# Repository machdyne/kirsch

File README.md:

# Kirsch Computer

Kirsch is an FPGA computer designed by Lone Dynamics Corporation.

This repo will contain schematics, PCB layouts, pinouts, a 3D-printable case, example gateware and documentation.

Find more information on the [Kirsch product page](https://machdyne.com/product/kirsch-computer/).

## Programming Kirsch

Kirsch has a JTAG interface that can be used to program the SRAM or the included flash [MMOD](https://machdyne.com/product/mmod).

### JTAG

These examples assume you're using a "USB Blaster" JTAG cable, see the header pinout below. You will need to have [openFPGALoader](https://github.com/trabucayre/openFPGALoader) installed.

Program the configuration SRAM:

```
openFPGALoader -c usb-blaster blinky.bit
```

Program the flash MMOD:

```
openFPGALoader -f -c usb-blaster blinky.bit --fpga-part xc7a35tftg256
```

## Blinky 

Building the blinky example requires Vivado or [openxc7](https://github.com/openxc7).

Assuming they are installed, you can simply type `make blinky_openxc7` or `make blinky_vivado` to build the gateware, which will be written to output/blinky.bit. You can then use [openFPGALoader](https://github.com/trabucayre/openFPGALoader) to write the gateware to the device.

## Linux

See the [Kakao Linux](https://github.com/machdyne/kakao) repo for the latest instructions.

### Prebuilt Images

Copy the files from the `images/linux` and `images/v0` directory to the root directory of a FAT-formatted MicroSD card along with the files from the `images` directory in the [Kakao Linux](https://github.com/machdyne/kakao) repo.

Kirsch ships with LiteX gateware on the user gateware section of the MMOD that is compatible with these images. After several seconds the Linux penguin should appear on the screen (HDMI) followed by a login prompt. A serial console is also available over the USB-C port.

**Note: If using the `kirsch_usbacm.bit` bitstream, Kirsch won't boot until you've opened a terminal program on the correct port. This is because DTR is currently used as a reset signal (see [valentyusb](https://github.com/litex-hub/valentyusb)). If you want to use Kirsch standalone, use `kirsch.bit` instead which uses the PMOD as a serial console.**

### Building Linux

Please follow the setup instructions in the [linux-on-litex-vexriscv](https://github.com/litex-hub/linux-on-litex-vexriscv) repo and then:

1. Build the Linux-capable gateware:

```
$ cd linux-on-litex-vexriscv
$ ./make.py --board kirsch --build
```

2. Write the gateware to the MMOD using USB DFU:

```
$ openFPGALoader -f -c usb-blaster build/kirsch/gateware/kirsch.bit --fpga-part xc7a35tftg256 
```
3. Copy the device tree binary `build/kirsch/kirsch.dtb` to a FAT-formatted MicroSD card.

4. Build the Linux kernel and root filesystem:

See the [Kakao Linux](https://github.com/machdyne/kakao?tab=readme-ov-file#optional-building-kakao-linux) repo for instructions.

5. Copy the Image and rootfs.cpio files generated in the previous step to the boot partition of the MicroSD card, in addition to the following files:

6. Copy the OpenSBI binary (included in this repo as `kirsch/images/linux/opensbi.bin`) to the MicroSD card. Alternatively, you can build this binary by following [these instructions](https://github.com/litex-hub/linux-on-litex-vexriscv#-generating-the-opensbi-binary-optional).

7. Copy `kirsch/images/linux/boot.json` to the MicroSD card.

8. Power-cycle Kirsch. After Linux has finished booting you should see a login prompt on the HDMI display.

## JTAG Header

The 3.3V JTAG header can be used to program the FPGA SRAM as well as the MMOD flash memory. It can also be used to provide power (5V) to the board.

```
1 2
3 4
5 6
```

| Pin | Signal |
| --- | ------ |
| 1 | TCK |
| 2 | TDI |
| 3 | TDO |
| 4 | TMS |
| 5 | 5V0 |
| 6 | GND |

## Board Revisions

| Revision | Notes |
| -------- | ----- |
| V0 | Initial version |

## License

The contents of this repo are released under the [Lone Dynamics Open License](LICENSE.md) with the following exceptions:

- The KiCad design files contain parts of the [kicad-pmod](https://github.com/mithro/kicad-pmod) library which is released under the [Apache License, Version 2.0](https://www.apache.org/licenses/LICENSE-2.0.html).

- The KiCad design files may contain symbols and footprints released under other licenses; please contact us if we've failed to give proper attribution.

Note: You can use these designs for commercial purposes but we ask that instead of producing exact clones, that you either replace our trademarks and logos with your own or add your own next to ours.

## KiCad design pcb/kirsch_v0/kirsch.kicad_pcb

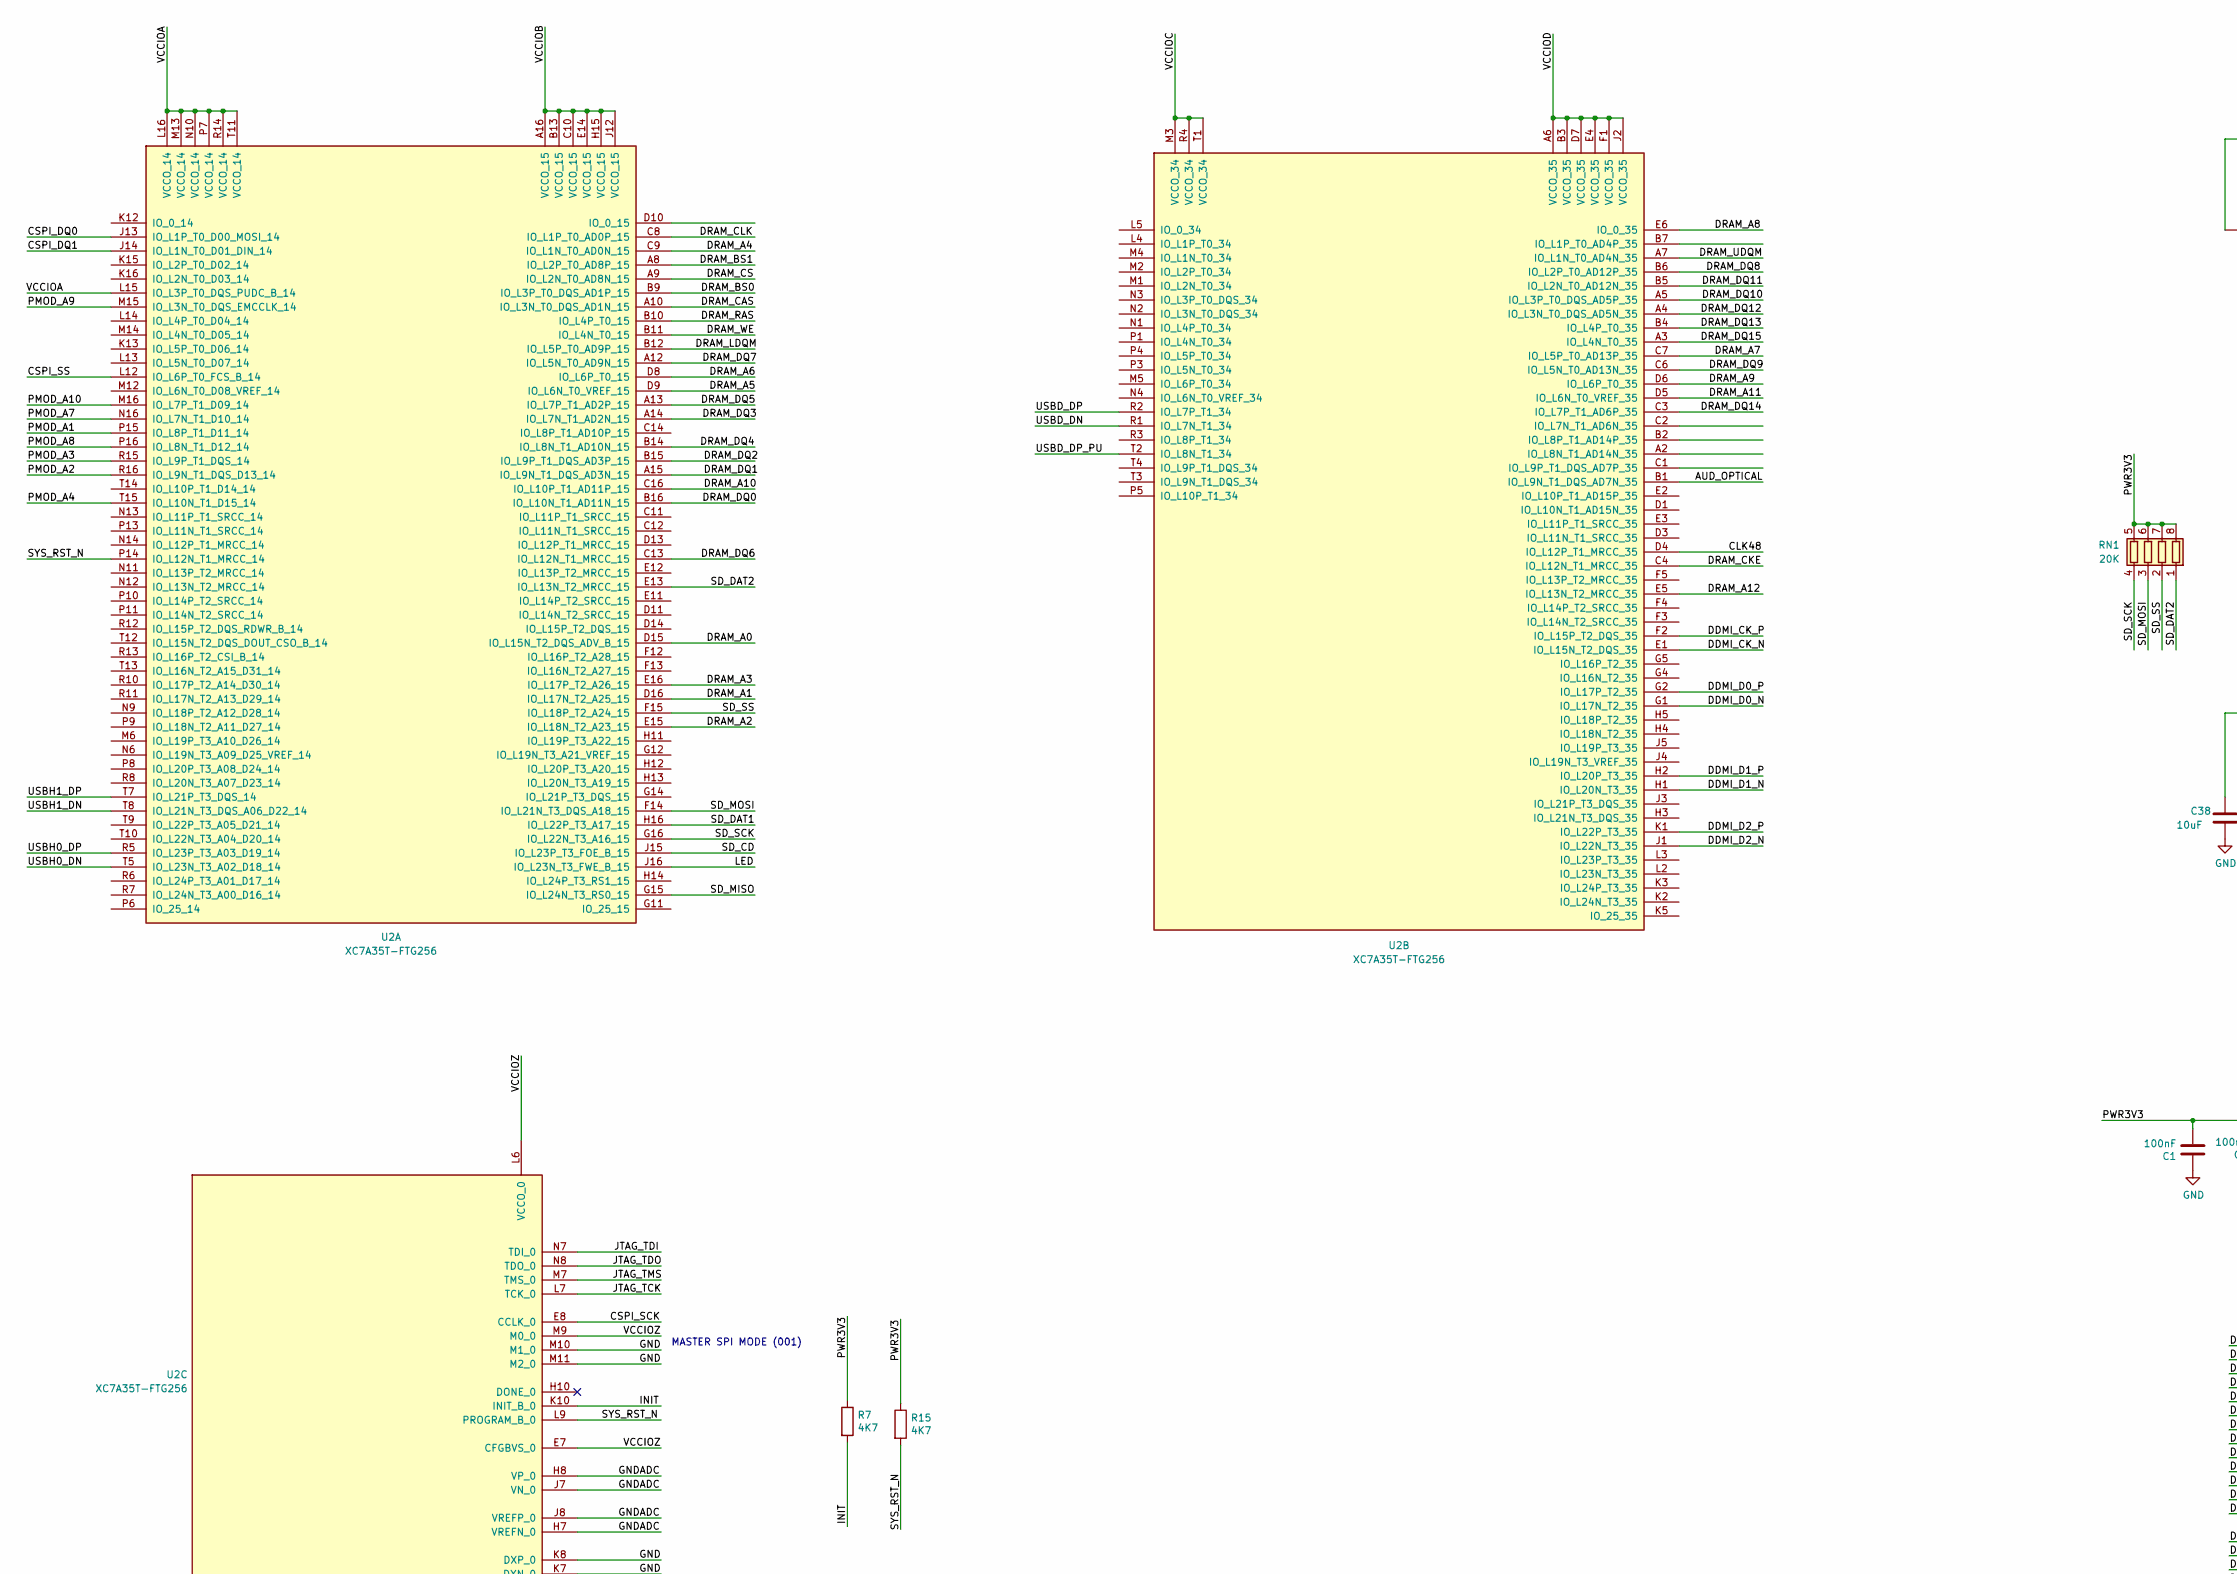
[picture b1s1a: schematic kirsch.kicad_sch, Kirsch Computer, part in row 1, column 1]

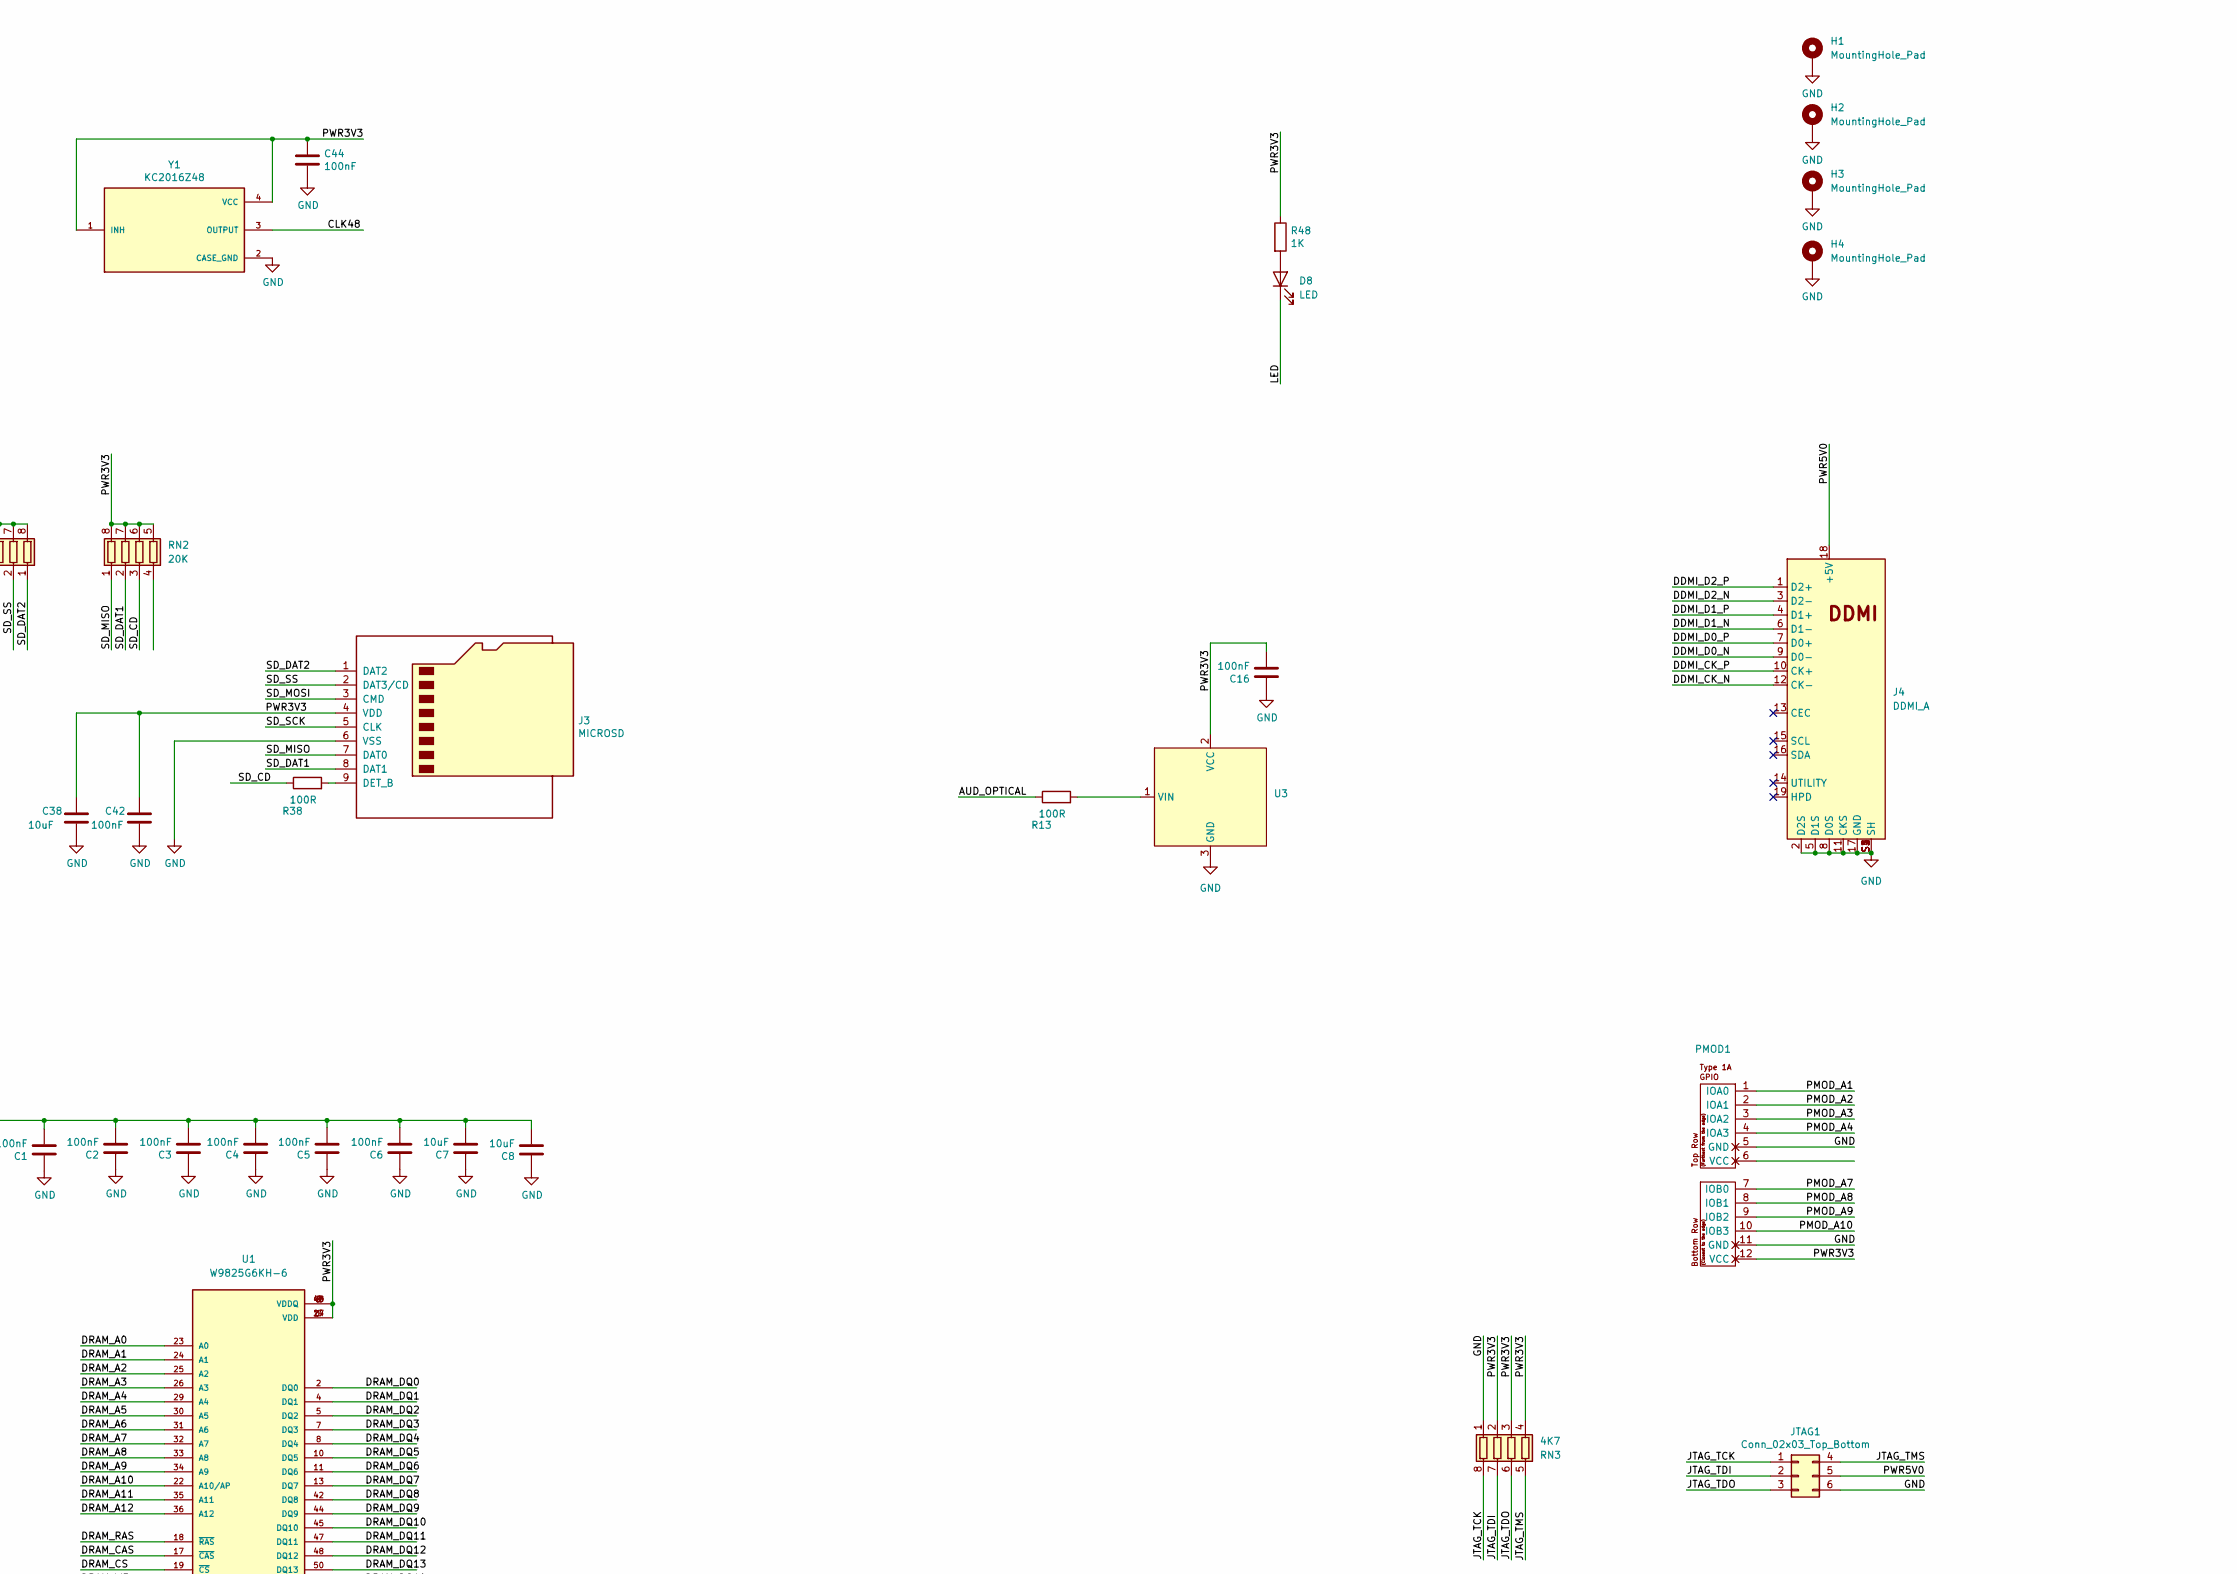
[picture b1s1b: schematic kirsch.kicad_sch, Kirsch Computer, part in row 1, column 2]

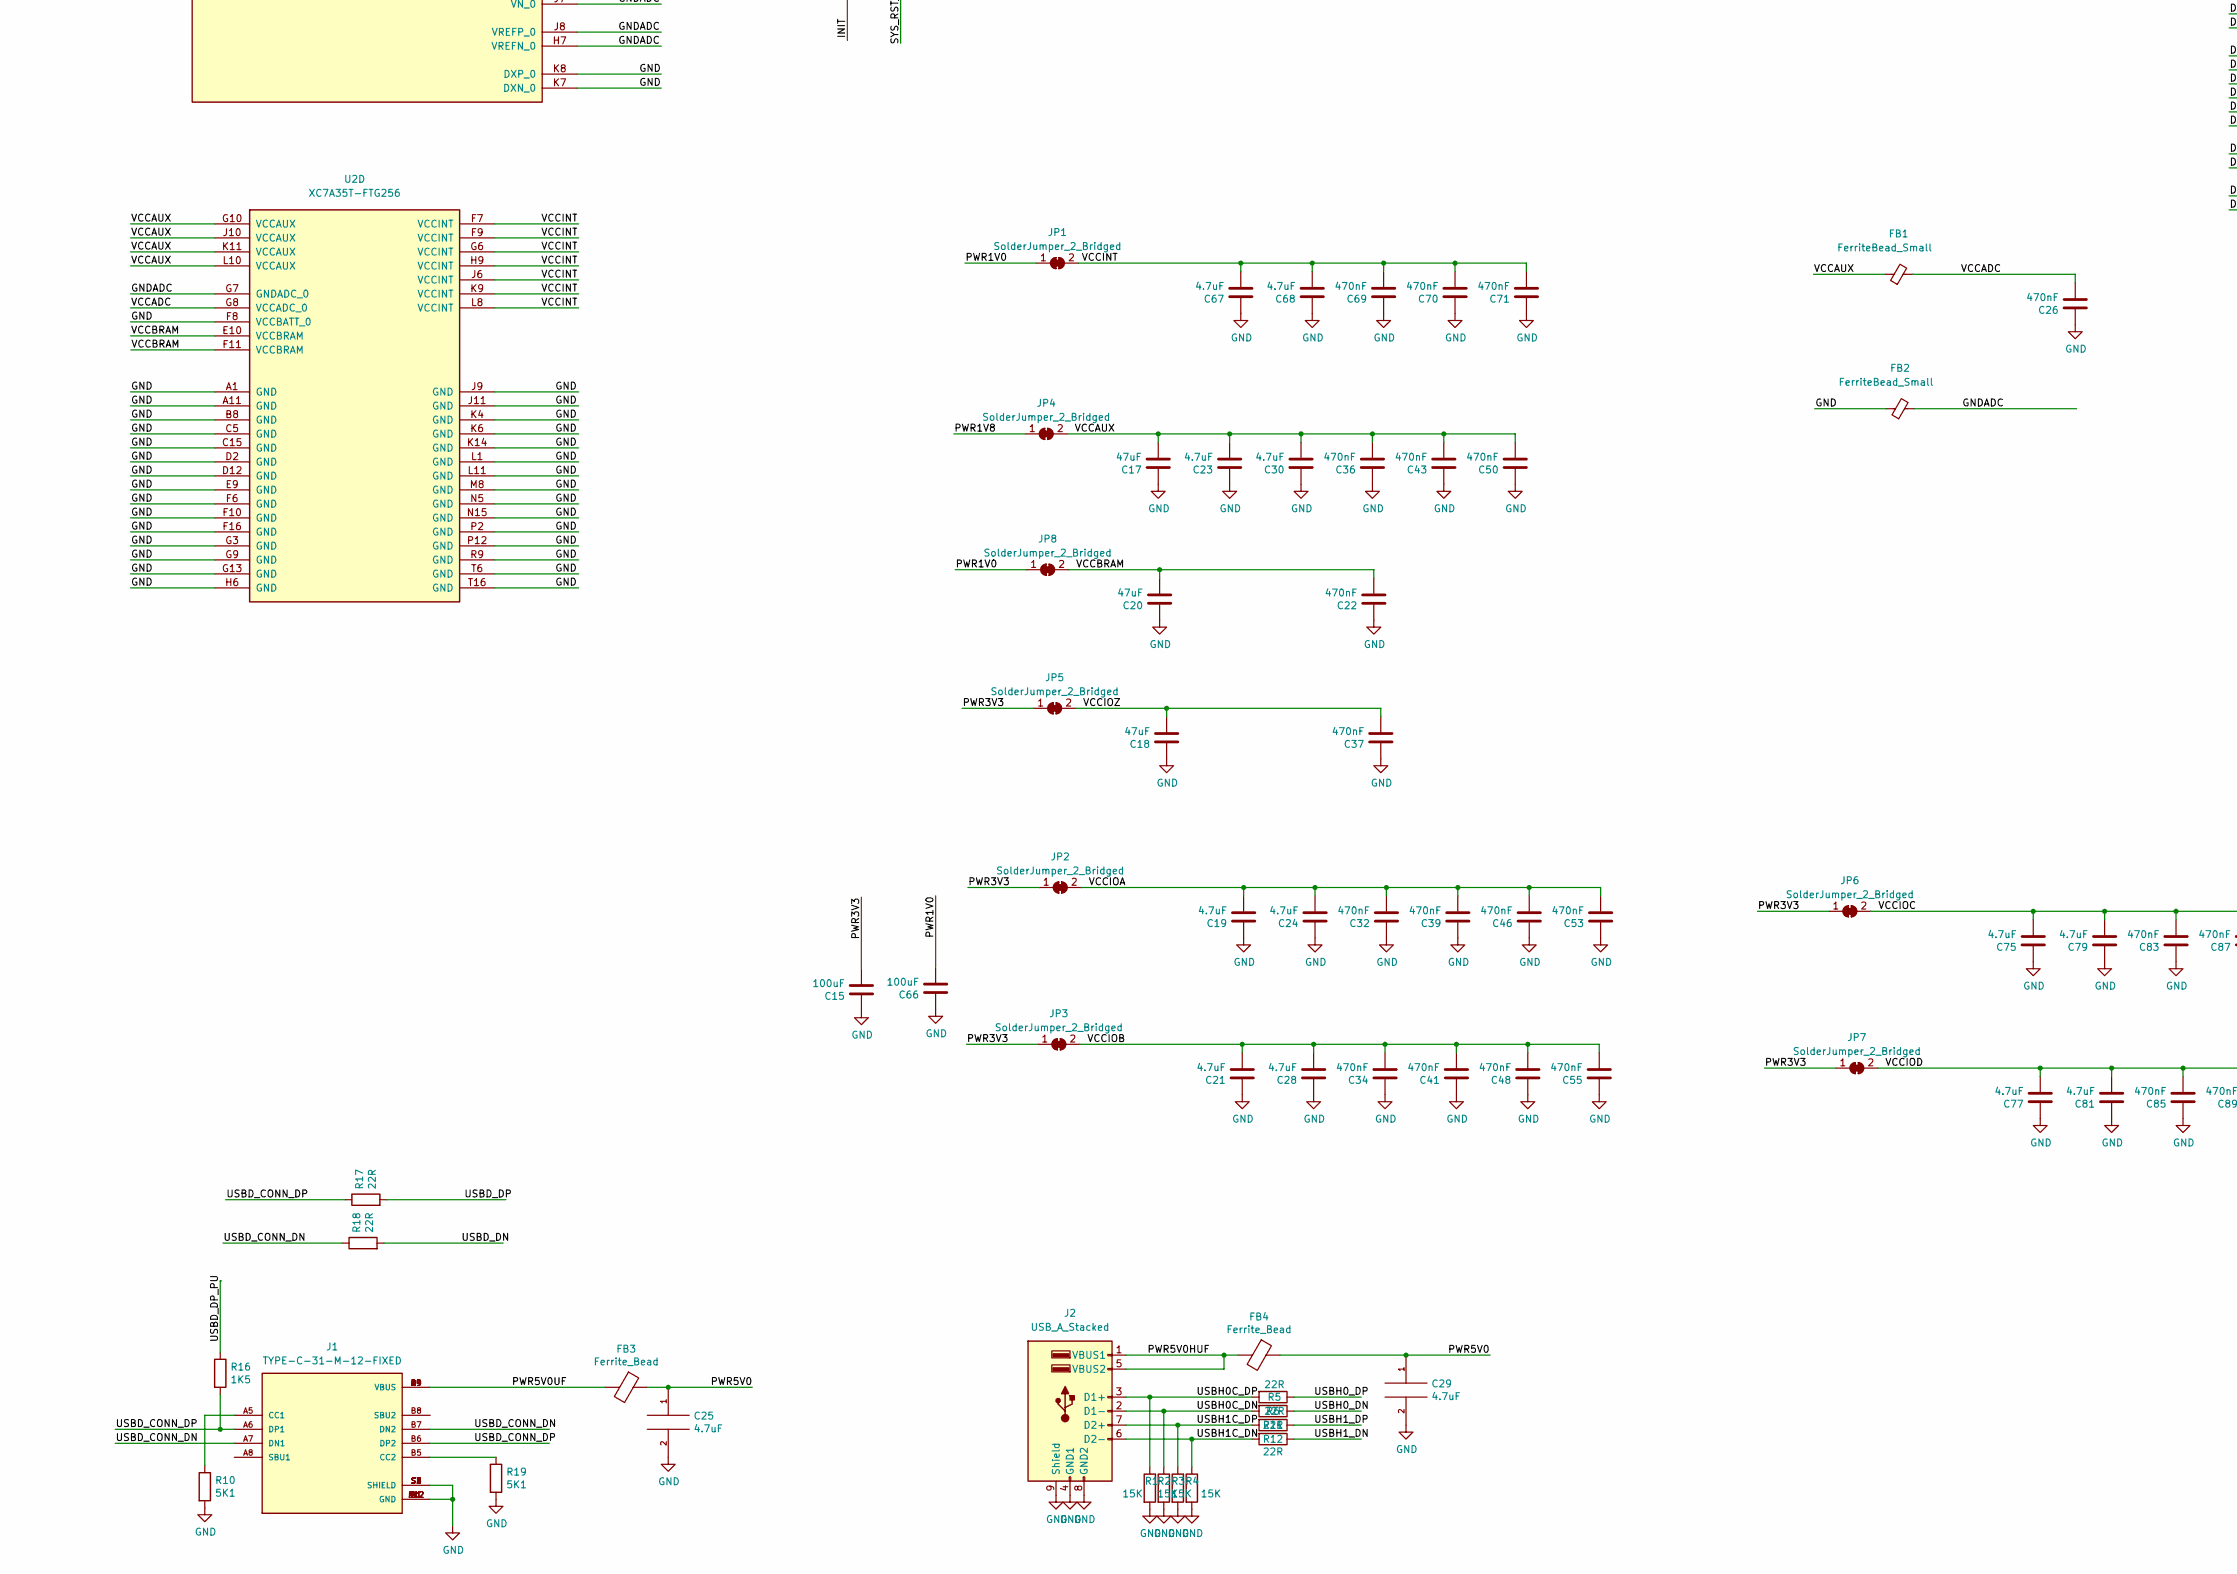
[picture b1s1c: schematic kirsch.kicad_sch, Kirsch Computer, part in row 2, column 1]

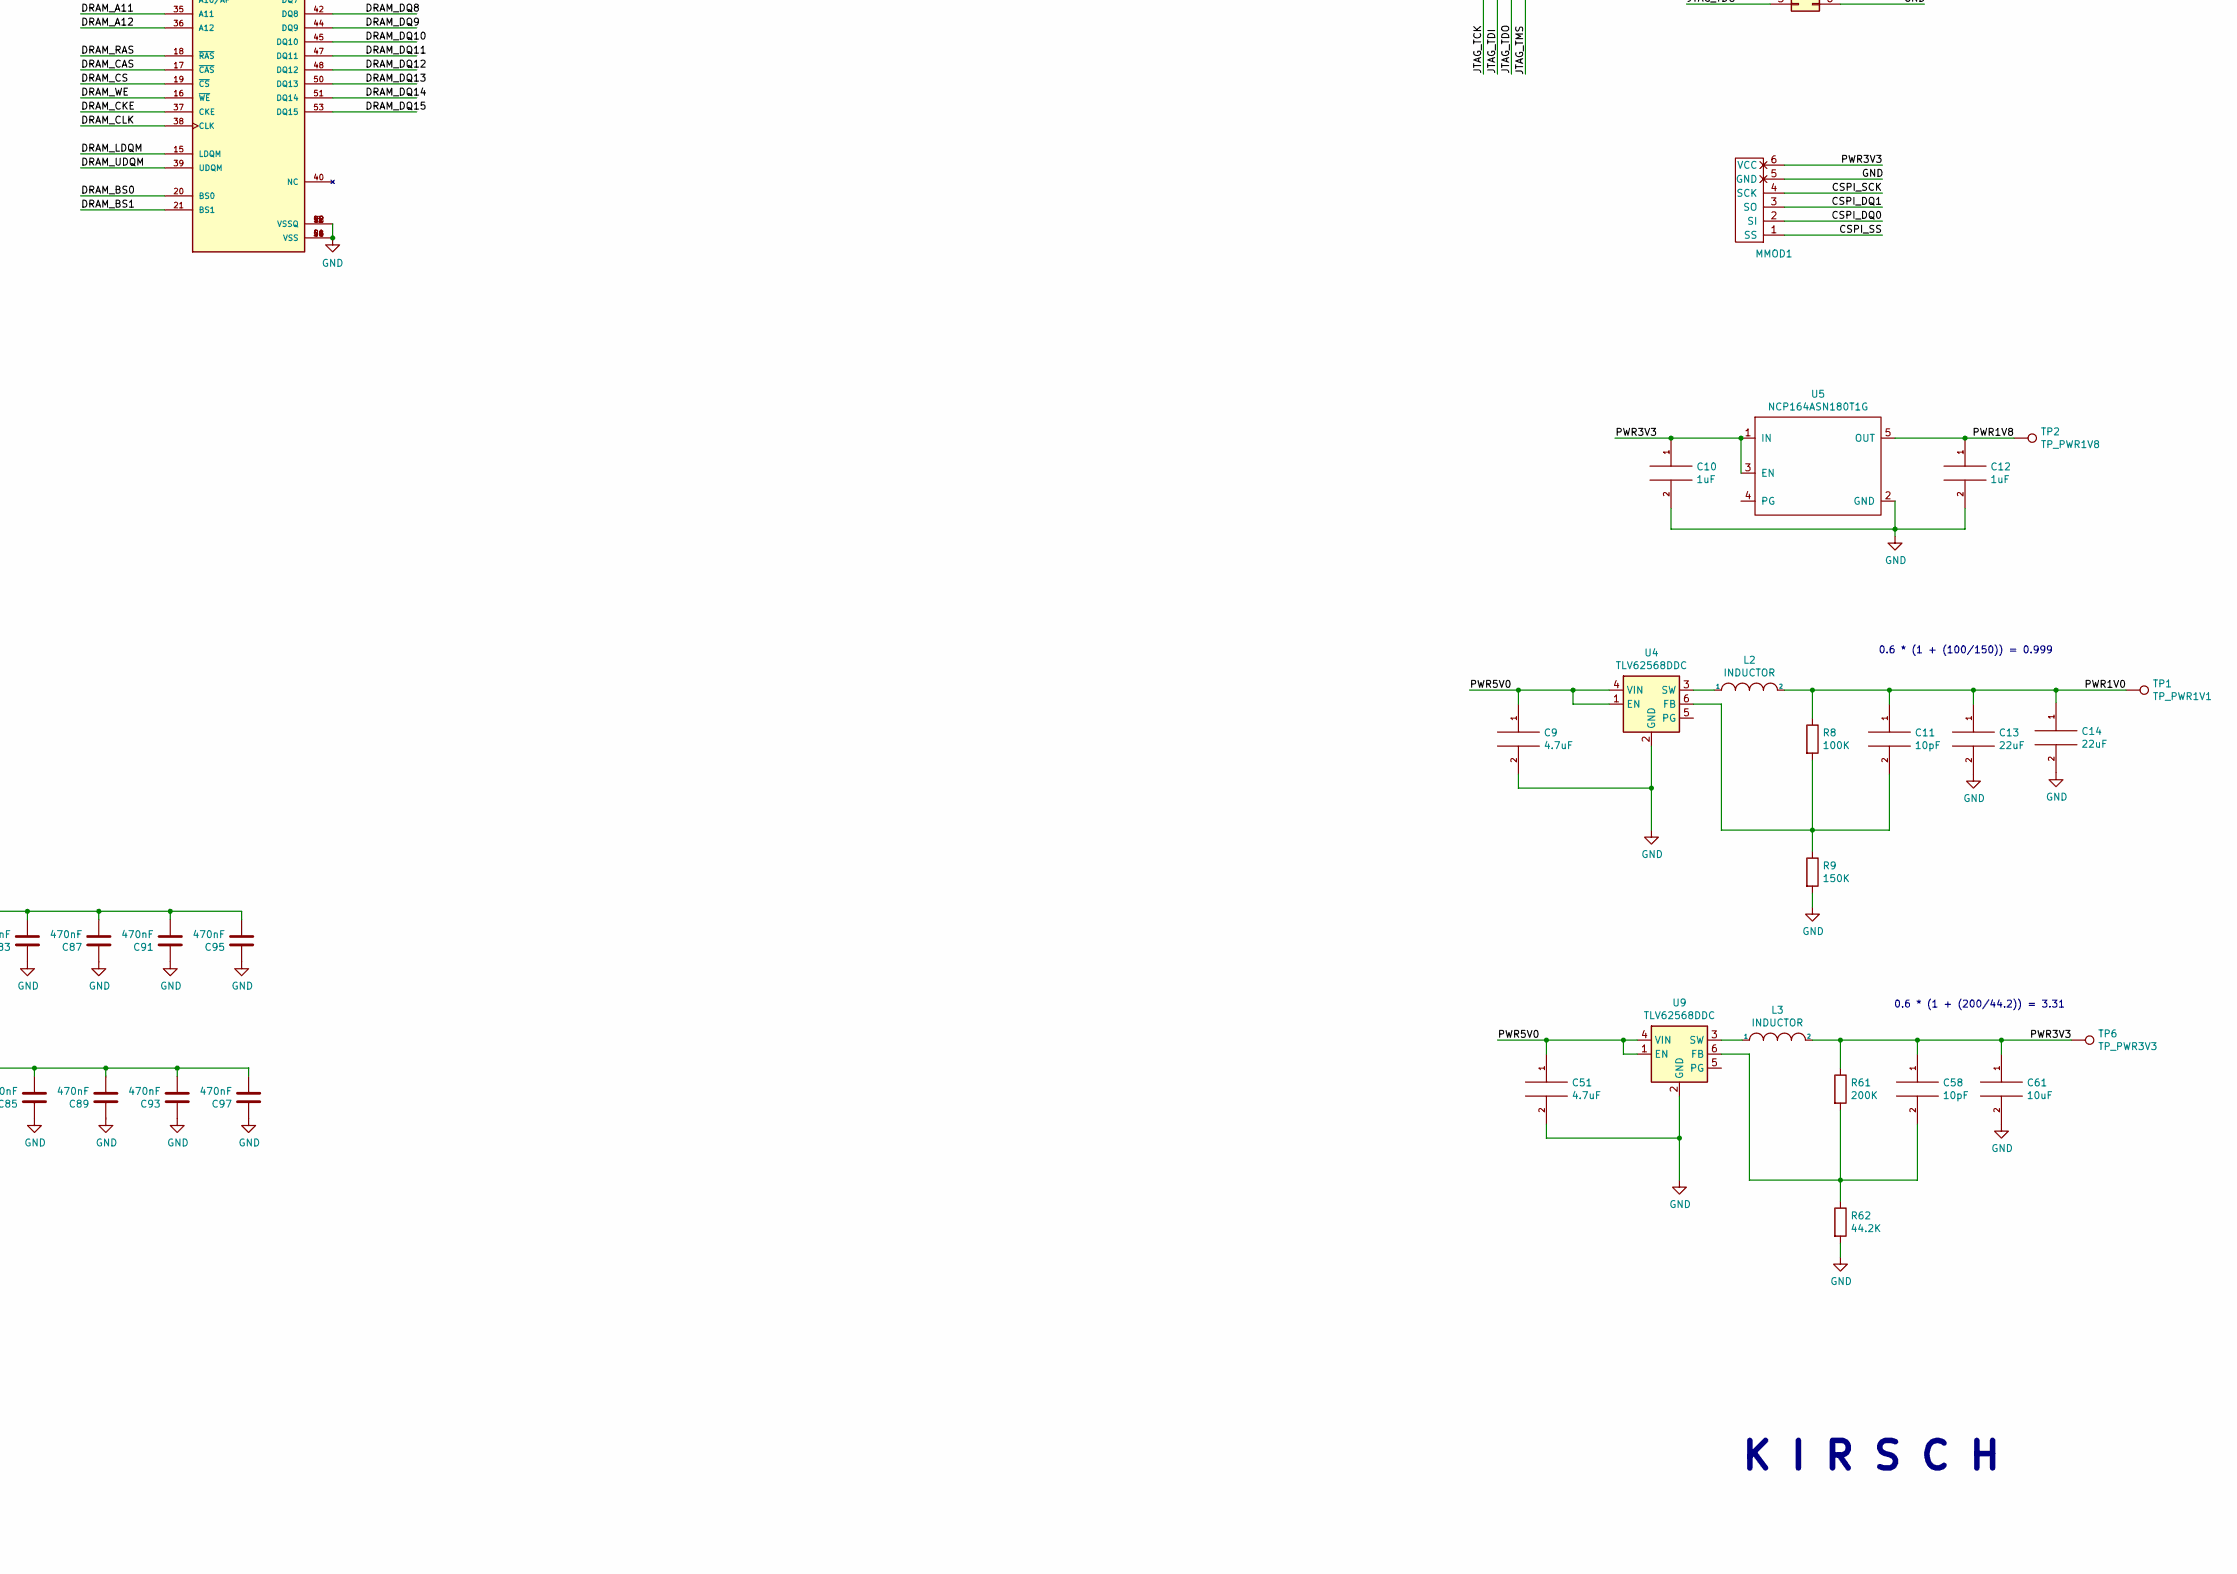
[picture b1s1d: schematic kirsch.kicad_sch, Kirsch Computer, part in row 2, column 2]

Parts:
C1, C2, C3, C4, C5, C6, C16, C42: 100nF; C_0603_1608Metric
C7, C8, C38, C61: 10uF; C_0603_1608Metric
C9, C19, C21, C23, C24, C25, C28, C29, C30, C51, C67, C68, C75, C77, C79, C81: 4.7uF; C_0603_1608Metric
C10, C12: 1uF; C_0603_1608Metric
C11, C58: 10pF; C_0603_1608Metric
C13, C14: 22uF; C_0603_1608Metric
C15, C66: 100uF; C_1206_3216Metric
C17, C18, C20: 47uF; C_0603_1608Metric
C22, C32, C34, C39, C41, C46, C83, C85, C87, C93: 470nF; C_0603_1608Metric
C26, C36, C37, C43, C48, C50, C53, C55, C69, C70, C71, C89, C91, C95, C97: 470nF; C_0402_1005Metric
C44: 100nF; R_0603_1608Metric
D8: LED; LED_1206_3216Metric
FB1, FB2: FerriteBead_Small; L_0402_1005Metric
FB3, FB4: Ferrite_Bead; R_0603_1608Metric
H1, H2, H3, H4: MountingHole_Pad; MountingHole_3.2mm_M3_Pad
J1: TYPE-C-31-M-12-FIXED; USB_C_Receptacle_HRO_TYPE-C-31-M-12-BIG-PADS; PARTREV A
J2: USB_A_Stacked; USB_A_Wuerth_61400826021_Horizontal_Stacked
J3: MICROSD; SDCARD
J4: DDMI_A; HDMI_TE_1827059-3-FIXED
JP1, JP2, JP3, JP4, JP5, JP6, JP7, JP8: SolderJumper_2_Bridged; LD-NETTIE-0603
JTAG1: Conn_02x03_Top_Bottom; PinHeader_2x03_P2.54mm_Vertical
L2, L3: INDUCTOR; L_0805_2012Metric
MMOD1: PMOD-Device-x1-Type-2-SPI; MMOD_Host_Socket_Vertical
PMOD1: PMOD-Device-x2-Type-1A-GPIO; PMOD_2x06_HOST
R1, R2, R3, R4: 15K; R_0402_1005Metric
R5, R6, R11, R12, R17, R18: 22R; R_0402_1005Metric
R7, R15: 4K7; R_0603_1608Metric
R8: 100K; R_0603_1608Metric
R9: 150K; R_0603_1608Metric
R10, R19: 5K1; R_0603_1608Metric
R13, R38: 100R; R_0603_1608Metric
R16: 1K5; R_0402_1005Metric
R48: 1K; R_0603_1608Metric
R61: 200K; R_0603_1608Metric
R62: 44.2K; R_0603_1608Metric
RN1, RN2: 20K; R_Array_Convex_4x0402
RN3: 4K7; R_Array_Convex_4x0402
TP1: TP_PWR1V1; TestPoint_THTPad_D1.0mm_Drill0.5mm
TP2: TP_PWR1V8; TestPoint_THTPad_D1.0mm_Drill0.5mm
TP6: TP_PWR3V3; TestPoint_THTPad_D1.0mm_Drill0.5mm
U1: W9825G6KH-6; SOP80P1176X120-54N; PARTREV A05
U2: XC7A35T-FTG256; BGA-256_17.0x17.0mm_Layout16x16_P1.0mm_Ball0.5mm_Pad0.5mm_N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
U3: ZGY133
U4, U9: TLV62568DDC; SOT-23-6
U5: NCP164ASN180T1G; SOT-23-5
Y1: KC2016Z48; OSC_KC2016Z13.5600C1KX00; PARTREV November 2020

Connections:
/AUD_OPTICAL: R13.1, U2.B1 (IO_L9N_T1_DQS_AD7N_35)
/CLK48: U2.D4 (IO_L12P_T1_MRCC_35), Y1.3 (OUTPUT)
/CSPI_DQ0: MMOD1.2 (SI), U2.J13 (IO_L1P_T0_D00_MOSI_14)
/CSPI_DQ1: MMOD1.3 (SO), U2.J14 (IO_L1N_T0_D01_DIN_14)
/CSPI_SCK: MMOD1.4 (SCK), U2.E8 (CCLK_0)
/CSPI_SS: MMOD1.1 (SS), U2.L12 (IO_L6P_T0_FCS_B_14); also elsewhere on the board
/DDMI_CK_N: J4.12 (CK-), U2.E1 (IO_L15N_T2_DQS_35)
/DDMI_CK_P: J4.10 (CK+), U2.F2 (IO_L15P_T2_DQS_35)
/DDMI_D0_N: J4.9 (D0-), U2.G1 (IO_L17N_T2_35)
/DDMI_D0_P: J4.7 (D0+), U2.G2 (IO_L17P_T2_35)
/DDMI_D1_N: J4.6 (D1-), U2.H1 (IO_L20N_T3_35)
/DDMI_D1_P: J4.4 (D1+), U2.H2 (IO_L20P_T3_35)
/DDMI_D2_N: J4.3 (D2-), U2.J1 (IO_L22N_T3_35)
/DDMI_D2_P: J4.1 (D2+), U2.K1 (IO_L22P_T3_35)
/DRAM_A0: U1.23 (A0), U2.D15 (IO_L15N_T2_DQS_ADV_B_15)
/DRAM_A1: U1.24 (A1), U2.D16 (IO_L17N_T2_A25_15)
/DRAM_A2: U1.25 (A2), U2.E15 (IO_L18N_T2_A23_15)
/DRAM_A3: U1.26 (A3), U2.E16 (IO_L17P_T2_A26_15)
/DRAM_A4: U1.29 (A4), U2.C9 (IO_L1N_T0_AD0N_15)
/DRAM_A5: U1.30 (A5), U2.D9 (IO_L6N_T0_VREF_15)
/DRAM_A6: U1.31 (A6), U2.D8 (IO_L6P_T0_15)
/DRAM_A7: U1.32 (A7), U2.C7 (IO_L5P_T0_AD13P_35)
/DRAM_A8: U1.33 (A8), U2.E6 (IO_0_35)
/DRAM_A9: U1.34 (A9), U2.D6 (IO_L6P_T0_35)
/DRAM_A10: U1.22 (A10/AP), U2.C16 (IO_L10P_T1_AD11P_15)
/DRAM_A11: U1.35 (A11), U2.D5 (IO_L6N_T0_VREF_35)
/DRAM_A12: U1.36 (A12), U2.E5 (IO_L13N_T2_MRCC_35)
/DRAM_BS0: U1.20 (BS0), U2.B9 (IO_L3P_T0_DQS_AD1P_15)
/DRAM_BS1: U1.21 (BS1), U2.A8 (IO_L2P_T0_AD8P_15)
/DRAM_CAS: U1.17 (~CAS), U2.A10 (IO_L3N_T0_DQS_AD1N_15)
/DRAM_CKE: U1.37 (CKE), U2.C4 (IO_L12N_T1_MRCC_35)
/DRAM_CLK: U1.38 (CLK), U2.C8 (IO_L1P_T0_AD0P_15)
/DRAM_CS: U1.19 (~CS), U2.A9 (IO_L2N_T0_AD8N_15)
/DRAM_DQ0: U1.2 (DQ0), U2.B16 (IO_L10N_T1_AD11N_15)
/DRAM_DQ1: U1.4 (DQ1), U2.A15 (IO_L9N_T1_DQS_AD3N_15)
/DRAM_DQ2: U1.5 (DQ2), U2.B15 (IO_L9P_T1_DQS_AD3P_15)
/DRAM_DQ3: U1.7 (DQ3), U2.A14 (IO_L7N_T1_AD2N_15)
/DRAM_DQ4: U1.8 (DQ4), U2.B14 (IO_L8N_T1_AD10N_15)
/DRAM_DQ5: U1.10 (DQ5), U2.A13 (IO_L7P_T1_AD2P_15)
/DRAM_DQ6: U1.11 (DQ6), U2.C13 (IO_L12N_T1_MRCC_15)
/DRAM_DQ7: U1.13 (DQ7), U2.A12 (IO_L5N_T0_AD9N_15)
/DRAM_DQ8: U1.42 (DQ8), U2.B6 (IO_L2P_T0_AD12P_35)
/DRAM_DQ9: U1.44 (DQ9), U2.C6 (IO_L5N_T0_AD13N_35)
/DRAM_DQ10: U1.45 (DQ10), U2.A5 (IO_L3P_T0_DQS_AD5P_35)
/DRAM_DQ11: U1.47 (DQ11), U2.B5 (IO_L2N_T0_AD12N_35)
/DRAM_DQ12: U1.48 (DQ12), U2.A4 (IO_L3N_T0_DQS_AD5N_35)
/DRAM_DQ13: U1.50 (DQ13), U2.B4 (IO_L4P_T0_35)
/DRAM_DQ14: U1.51 (DQ14), U2.C3 (IO_L7P_T1_AD6P_35)
/DRAM_DQ15: U1.53 (DQ15), U2.A3 (IO_L4N_T0_35)
/DRAM_LDQM: U1.15 (LDQM), U2.B12 (IO_L5P_T0_AD9P_15)
/DRAM_RAS: U1.18 (~RAS), U2.B10 (IO_L4P_T0_15)
/DRAM_UDQM: U1.39 (UDQM), U2.A7 (IO_L1N_T0_AD4N_35)
/DRAM_WE: U1.16 (~WE), U2.B11 (IO_L4N_T0_15)
/ETH_RST_N: U2.H4 (IO_L18N_T2_35)
/GNDADC: FB2.2, U2.G7 (GNDADC_0), U2.H7 (VREFN_0), U2.H8 (VP_0), U2.J7 (VN_0), U2.J8 (VREFP_0)
/INIT: R7.2, U2.K10 (INIT_B_0)
/JTAG_TCK: JTAG1.1, RN3.8 (R1.2), U2.L7 (TCK_0)
/JTAG_TDI: JTAG1.2, RN3.7 (R2.2), U2.N7 (TDI_0)
/JTAG_TDO: JTAG1.3, RN3.6 (R3.2), U2.N8 (TDO_0)
/JTAG_TMS: JTAG1.4, RN3.5 (R4.2), U2.M7 (TMS_0)
/LED: D8.1 (K), U2.J16 (IO_L23N_T3_FWE_B_15)
/PMOD_A1: PMOD1.1 (IOA0), U2.P15 (IO_L8P_T1_D11_14)
/PMOD_A2: PMOD1.2 (IOA1), U2.R16 (IO_L9N_T1_DQS_D13_14)
/PMOD_A3: PMOD1.3 (IOA2), U2.R15 (IO_L9P_T1_DQS_14)
/PMOD_A4: PMOD1.4 (IOA3), U2.T15 (IO_L10N_T1_D15_14)
/PMOD_A7: PMOD1.7 (IOB0), U2.N16 (IO_L7N_T1_D10_14)
/PMOD_A8: PMOD1.8 (IOB1), U2.P16 (IO_L8N_T1_D12_14)
/PMOD_A9: PMOD1.9 (IOB2), U2.M15 (IO_L3N_T0_DQS_EMCCLK_14)
/PMOD_A10: PMOD1.10 (IOB3), U2.M16 (IO_L7P_T1_D09_14)
/PWR1V0: C11.1, C13.1, C14.1, C66.2, JP1.1 (A), JP8.1 (A), L2.2, R8.1, TP1.1
/PWR1V8: C12.1, JP4.1 (A), TP2.1, U5.5 (OUT)
/PWR3V3: C1.2, C2.2, C3.2, C4.2, C5.2, C6.2, C7.2, C8.2, C10.1, C15.2, C16.2, C38.1, C42.1, C44.1, C58.1, C61.1, J3.4 (VDD), JP2.1 (A), JP3.1 (A), JP5.1 (A), JP6.1 (A), JP7.1 (A), L3.2, MMOD1.6 (VCC), PMOD1.12 (VCC), R7.1, R15.1, R48.1, R61.1, RN1.5 (R4.2), RN1.6 (R3.2), RN1.7 (R2.2), RN1.8 (R1.2), RN2.5 (R4.2), RN2.6 (R3.2), RN2.7 (R2.2), RN2.8 (R1.2), RN3.2 (R2.1), RN3.3 (R3.1), RN3.4 (R4.1), TP6.1, U1.1 (VDD), U1.3 (VDDQ), U1.9 (VDDQ), U1.14 (VDD), U1.27 (VDD), U1.43 (VDDQ), U1.49 (VDDQ), U3.2 (VCC), U5.1 (IN), U5.3 (EN), Y1.1 (INH), Y1.4 (VCC); also elsewhere on the board
/PWR5V0: C9.1, C25.1, C29.1, C51.1, FB3.1, FB4.1, J4.18 (+5V), JTAG1.5, U4.1 (EN), U4.4 (VIN), U9.1 (EN), U9.4 (VIN)
/PWR5V0HUF: FB4.2, J2.1 (VBUS1), J2.5 (VBUS2)
/PWR5V0UF: FB3.2, J1.A4 (VBUS), J1.A9 (VBUS), J1.B4 (VBUS), J1.B9 (VBUS)
/SD_CD: R38.1, RN2.3 (R3.1), U2.J15 (IO_L23P_T3_FOE_B_15)
/SD_DAT1: J3.8 (DAT1), RN2.2 (R2.1), U2.H16 (IO_L22P_T3_A17_15)
/SD_DAT2: J3.1 (DAT2), RN1.1 (R1.1), U2.E13 (IO_L13N_T2_MRCC_15)
/SD_MISO: J3.7 (DAT0), RN2.1 (R1.1), U2.G15 (IO_L24N_T3_RS0_15)
/SD_MOSI: J3.3 (CMD), RN1.3 (R3.1), U2.F14 (IO_L21N_T3_DQS_A18_15)
/SD_SCK: J3.5 (CLK), RN1.4 (R4.1), U2.G16 (IO_L22N_T3_A16_15)
/SD_SS: J3.2 (DAT3/CD), RN1.2 (R2.1), U2.F15 (IO_L18P_T2_A24_15)
/SYS_RST_N: R15.2, U2.L9 (PROGRAM_B_0), U2.P14 (IO_L12N_T1_MRCC_14)
/USBD_CONN_DN: J1.A7 (DN1), J1.B7 (DN2), R18.1
/USBD_CONN_DP: J1.A6 (DP1), J1.B6 (DP2), R16.2, R17.1
/USBD_DN: R18.2, U2.R1 (IO_L7N_T1_34)
/USBD_DP: R17.2, U2.R2 (IO_L7P_T1_34)
/USBD_DP_PU: R16.1, U2.T2 (IO_L8N_T1_34)
/USBH0C_DN: J2.2 (D1-), R2.1, R6.2
/USBH0C_DP: J2.3 (D1+), R1.1, R5.2
/USBH0_DN: R6.1, U2.T5 (IO_L23N_T3_A02_D18_14)
/USBH0_DP: R5.1, U2.R5 (IO_L23P_T3_A03_D19_14)
/USBH1C_DN: J2.6 (D2-), R4.1, R12.2
/USBH1C_DP: J2.7 (D2+), R3.1, R11.2
/USBH1_DN: R12.1, U2.T8 (IO_L21N_T3_DQS_A06_D22_14)
/USBH1_DP: R11.1, U2.T7 (IO_L21P_T3_DQS_14)
/VCCADC: C26.2, FB1.2, U2.G8 (VCCADC_0)
/VCCAUX: C17.2, C23.2, C30.2, C36.2, C43.2, C50.2, FB1.1, JP4.2 (B), U2.G10 (VCCAUX), U2.J10 (VCCAUX), U2.K11 (VCCAUX), U2.L10 (VCCAUX)
/VCCBRAM: C20.2, C22.2, JP8.2 (B), U2.E10 (VCCBRAM), U2.F11 (VCCBRAM)
/VCCINT: C67.2, C68.2, C69.2, C70.2, C71.2, JP1.2 (B), U2.F7 (VCCINT), U2.F9 (VCCINT), U2.G6 (VCCINT), U2.H9 (VCCINT), U2.J6 (VCCINT), U2.K9 (VCCINT), U2.L8 (VCCINT)
/VCCIOA: C19.2, C24.2, C32.2, C39.2, C46.2, C53.2, JP2.2 (B), U2.L15 (IO_L3P_T0_DQS_PUDC_B_14), U2.L16 (VCCO_14), U2.M13 (VCCO_14), U2.N10 (VCCO_14), U2.P7 (VCCO_14), U2.R14 (VCCO_14), U2.T11 (VCCO_14)
/VCCIOB: C21.2, C28.2, C34.2, C41.2, C48.2, C55.2, JP3.2 (B), U2.A16 (VCCO_15), U2.B13 (VCCO_15), U2.C10 (VCCO_15), U2.E14 (VCCO_15), U2.H15 (VCCO_15), U2.J12 (VCCO_15)
/VCCIOC: C75.2, C79.2, C83.2, C87.2, C91.2, C95.2, JP6.2 (B), U2.M3 (VCCO_34), U2.R4 (VCCO_34), U2.T1 (VCCO_34)
/VCCIOD: C77.2, C81.2, C85.2, C89.2, C93.2, C97.2, JP7.2 (B), U2.A6 (VCCO_35), U2.B3 (VCCO_35), U2.D7 (VCCO_35), U2.E4 (VCCO_35), U2.F1 (VCCO_35), U2.J2 (VCCO_35)
/VCCIOZ: C18.2, C37.2, JP5.2 (B), U2.E7 (CFGBVS_0), U2.L6 (VCCO_0), U2.M9 (M0_0)
GND: C1.1, C2.1, C3.1, C4.1, C5.1, C6.1, C7.1, C8.1, C9.2, C10.2, C12.2, C13.2, C14.2, C15.1, C16.1, C17.1, C18.1, C19.1, C20.1, C21.1, C22.1, C23.1, C24.1, C25.2, C26.1, C28.1, C29.2, C30.1, C32.1, C34.1, C36.1, C37.1, C38.2, C39.1, C41.1, C42.2, C43.1, C44.2, C46.1, C48.1, C50.1, C51.2, C53.1, C55.1, C61.2, C66.1, C67.1, C68.1, C69.1, C70.1, C71.1, C75.1, C77.1, C79.1, C81.1, C83.1, C85.1, C87.1, C89.1, C91.1, C93.1, C95.1, C97.1, FB2.1, H1.1, H2.1, H3.1, H4.1, J1.A1 (GND), J1.A12 (GND), J1.B1 (GND), J1.B12 (GND), J1.S1 (SHIELD), J1.S2 (SHIELD), J1.S3 (SHIELD), J1.S4 (SHIELD), J2.4 (GND1), J2.8 (GND2), J2.9 (Shield), J3.6 (VSS), J4.2 (D2S), J4.5 (D1S), J4.8 (D0S), J4.11 (CKS), J4.17 (GND), J4.S1 (SH), J4.S2 (SH), J4.S3 (SH), J4.S4 (SH), JTAG1.6, MMOD1.5 (GND), PMOD1.5 (GND), PMOD1.11 (GND), R1.2, R2.2, R3.2, R4.2, R9.2, R10.2, R19.2, R62.2, RN3.1 (R1.1), U1.6 (VSSQ), U1.12 (VSSQ), U1.28 (VSS), U1.41 (VSS), U1.46 (VSSQ), U1.52 (VSSQ), U1.54 (VSS), U2.A1 (GND), U2.A11 (GND), U2.B8 (GND), U2.C5 (GND), U2.C15 (GND), U2.D2 (GND), U2.D12 (GND), U2.E9 (GND), U2.F6 (GND), U2.F8 (VCCBATT_0), U2.F10 (GND), U2.F16 (GND), U2.G3 (GND), U2.G9 (GND), U2.G13 (GND), U2.H6 (GND), U2.J9 (GND), U2.J11 (GND), U2.K4 (GND), U2.K6 (GND), U2.K7 (DXN_0), U2.K8 (DXP_0), U2.K14 (GND), U2.L1 (GND), U2.L11 (GND), U2.M8 (GND), U2.M10 (M1_0), U2.M11 (M2_0), U2.N5 (GND), U2.N15 (GND), U2.P2 (GND), U2.P12 (GND), U2.R9 (GND), U2.T6 (GND), U2.T16 (GND), U3.3 (GND), U4.2 (GND), U5.2 (GND), U9.2 (GND), Y1.2 (CASE_GND)
unnamed: D8.2 (A), R48.2
unnamed: J1.A5 (CC1), R10.1
unnamed: J1.B5 (CC2), R19.1
unnamed: J3.9 (DET_B), R38.2
unnamed: R13.2, U3.1 (VIN)
unnamed: C11.2, R8.2, R9.1, U4.6 (FB)
unnamed: L2.1, U4.3 (SW)
unnamed: C58.2, R61.2, R62.1, U9.6 (FB)
unnamed: L3.1, U9.3 (SW)

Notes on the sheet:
K I R S C H
0.6 * (1 + (200/44.2)) = 3.31
0.6 * (1 + (100/150)) = 0.999
MASTER SPI MODE (001)

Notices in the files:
pcb/kirsch_v0/kirsch.kicad_sch:
Copyright © 2024 Lone Dynamics Corporation
